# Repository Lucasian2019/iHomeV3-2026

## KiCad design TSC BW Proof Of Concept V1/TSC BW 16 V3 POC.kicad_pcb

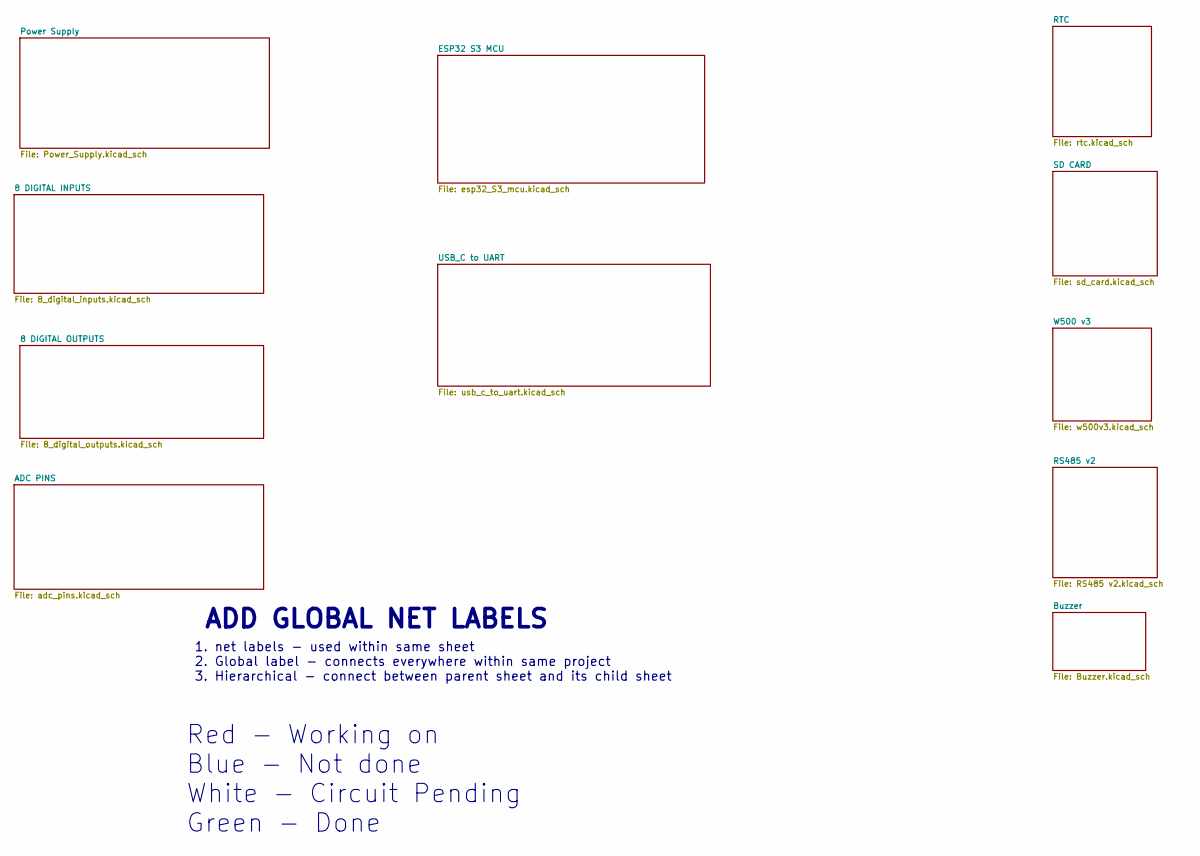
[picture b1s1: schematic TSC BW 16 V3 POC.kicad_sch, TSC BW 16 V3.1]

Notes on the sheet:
ADD GLOBAL NET LABELS
1. net labels - used within same sheet 2. Global label - connects everywhere within same project 3. Hierarchical - connect between parent sheet and its child sheet
Red - Working on Blue - Not done White - Circuit Pending Green - Done

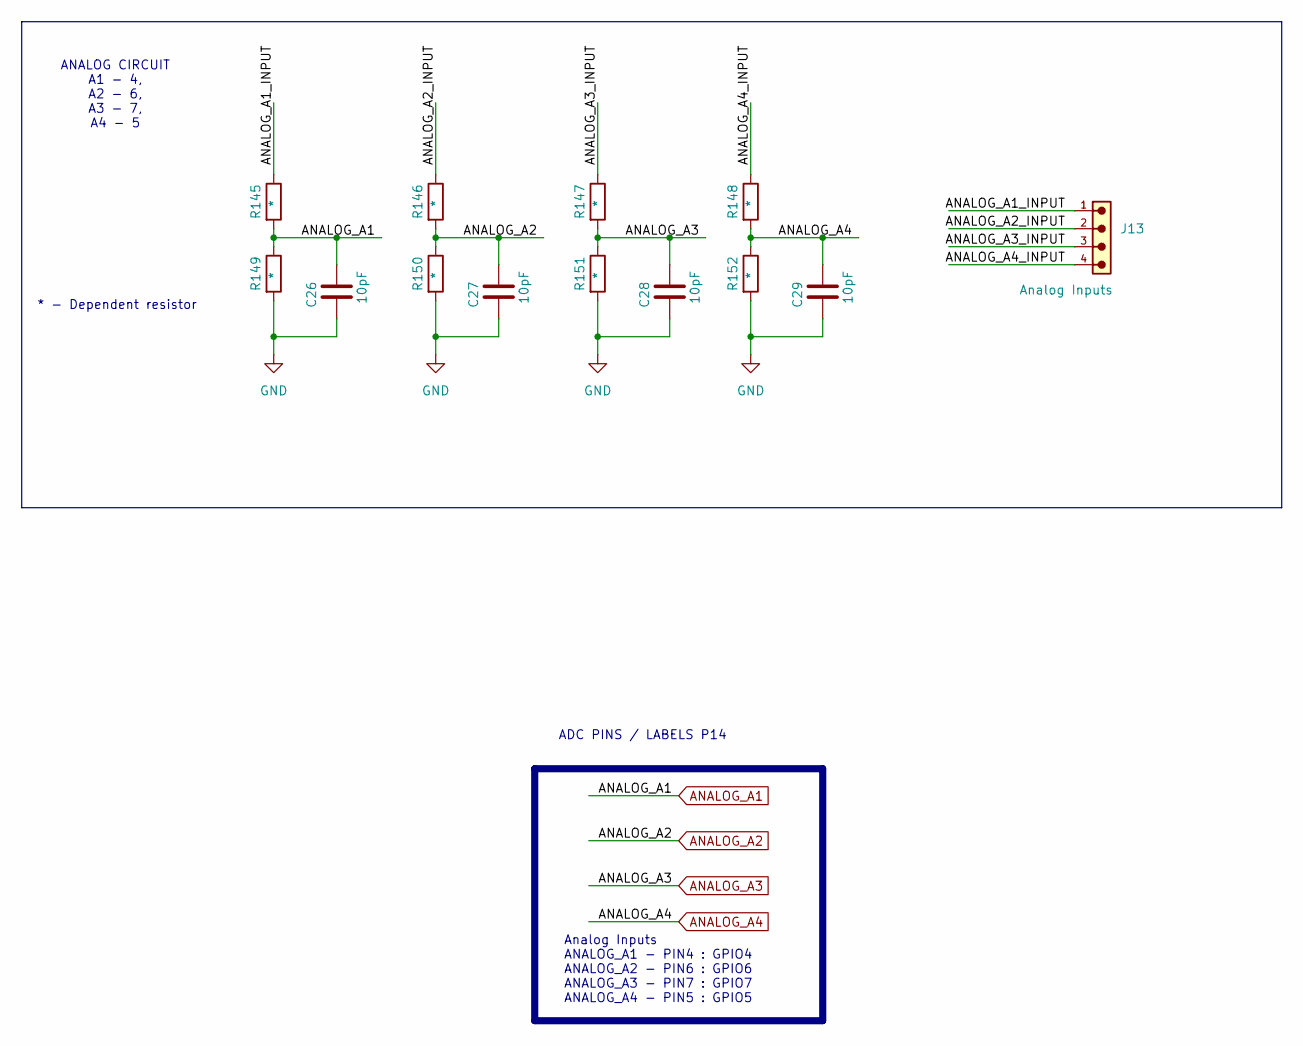
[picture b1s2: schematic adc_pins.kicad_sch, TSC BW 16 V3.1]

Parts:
C26, C27, C28, C29: 10pF; C_1206_3216Metric
J13: Analog Inputs; PhoenixContact_MSTBA_2,5_4-G-5,08_1x04_P5.08mm_Horizontal
R145, R146, R147, R148, R149, R150, R151, R152: *; R_1206_3216Metric_Pad1.30x1.75mm_HandSolder

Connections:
/ADC PINS/ANALOG_A1_INPUT: J13.1, R145.1
/ADC PINS/ANALOG_A2_INPUT: J13.2, R146.1
/ADC PINS/ANALOG_A3_INPUT: J13.3, R147.1
/ADC PINS/ANALOG_A4_INPUT: J13.4, R148.1
ANALOG_A1: C26.2, R145.2, R149.1; also elsewhere on the board
ANALOG_A2: C27.2, R146.2, R150.1; also elsewhere on the board
ANALOG_A3: C28.2, R147.2, R151.1; also elsewhere on the board
ANALOG_A4: C29.2, R148.2, R152.1; also elsewhere on the board
GND: C26.1, C27.1, C28.1, C29.1, R149.2, R150.2, R151.2, R152.2; also elsewhere on the board

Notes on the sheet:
ADC PINS / LABELS P14
Analog Inputs ANALOG_A1 - PIN4 : GPIO4 ANALOG_A2 - PIN6 : GPIO6 ANALOG_A3 - PIN7 : GPIO7 ANALOG_A4 - PIN5 : GPIO5
ANALOG CIRCUIT A1 - 4, A2 - 6, A3 - 7, A4 - 5
* - Dependent resistor

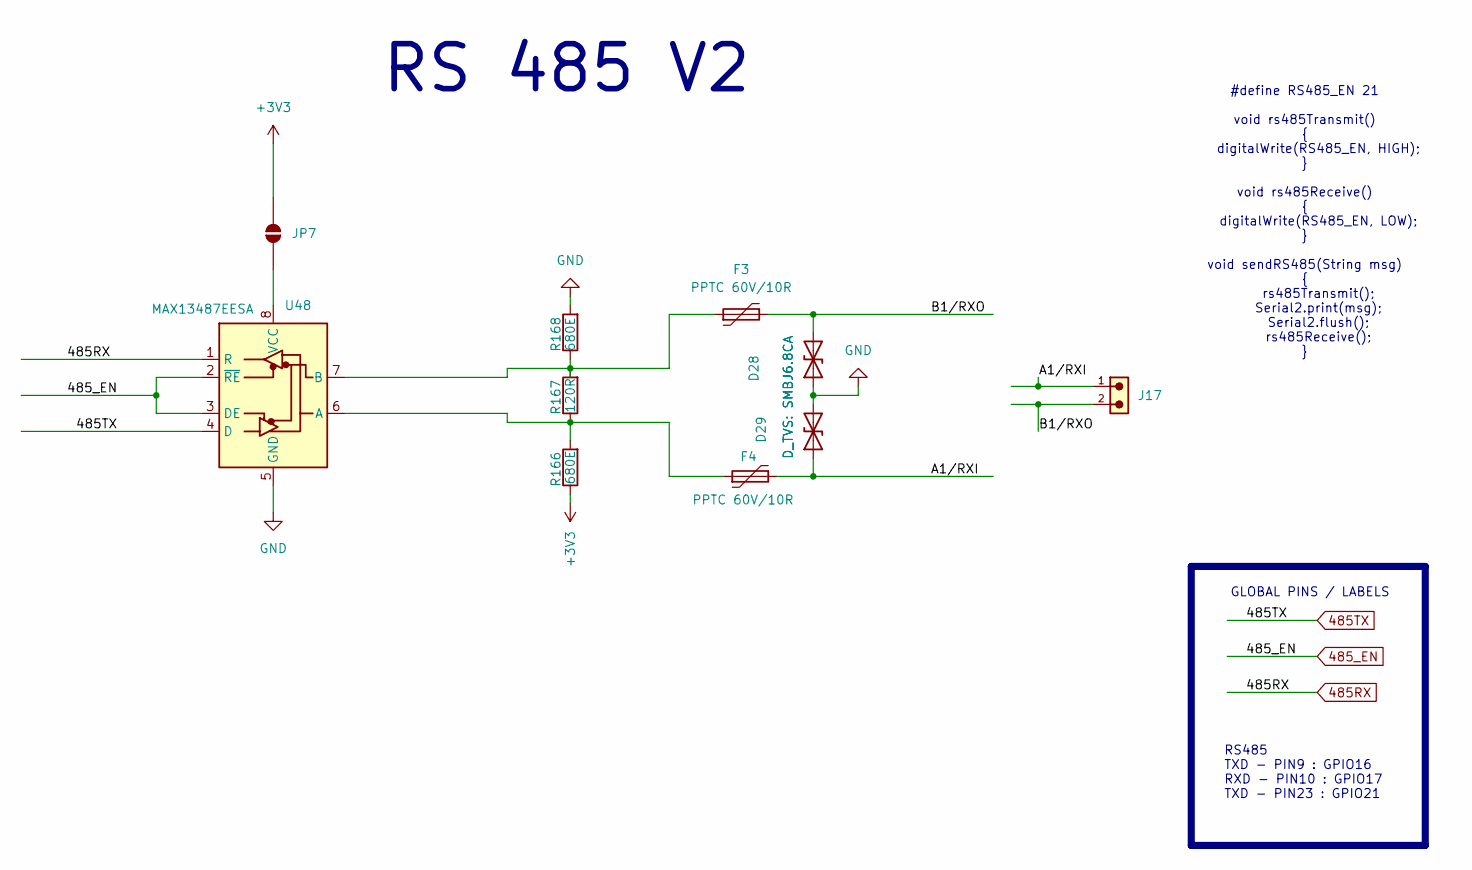
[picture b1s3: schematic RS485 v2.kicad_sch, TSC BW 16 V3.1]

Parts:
D28, D29: D_TVS: SMBJ6.8CA; D_SMB
F3, F4: PPTC 60V/10R; Fuse_1206_3216Metric
J17: 691312510002; PhoenixContact_MSTBA_2,5_2-G-5,08_1x02_P5.08mm_Horizontal
JP7: SolderJumper_2_Open; SolderJumper-2_P1.3mm_Open_RoundedPad1.0x1.5mm
R166, R168: 680E; R_1206_3216Metric_Pad1.30x1.75mm_HandSolder
R167: 120R; R_1206_3216Metric_Pad1.30x1.75mm_HandSolder
U48: MAX13487EESA; SOIC-8_3.9x4.9mm_P1.27mm

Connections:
485RX: U48.1 (R); also elsewhere on the board
485TX: U48.4 (D); also elsewhere on the board
485_EN: U48.2 (~RE), U48.3 (DE); also elsewhere on the board
+3V3: JP7.1 (A), R166.1; also elsewhere on the board
/RS485 v2/A1/RXI: D29.1 (A1), F4.2, J17.1
/RS485 v2/B1/RXO: D28.2 (A2), F3.2, J17.2
GND: D28.1 (A1), D29.2 (A2), R168.2, U48.5 (GND); also elsewhere on the board
unnamed: JP7.2 (B), U48.8 (VCC)
unnamed: F4.1, R166.2, R167.1, U48.6 (A)
unnamed: F3.1, R167.2, R168.1, U48.7 (B)

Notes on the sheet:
RS 485 V2
GLOBAL PINS / LABELS
#define RS485_EN 21 void rs485Transmit() { digitalWrite(RS485_EN, HIGH); } void rs485Receive() { digitalWrite(RS485_EN, LOW); } void sendRS485(String msg) { rs485Transmit(); Serial2.print(msg); Serial2.flush(); rs485Receive(); }
RS485 TXD - PIN9 : GPIO16 RXD - PIN10 : GPIO17 TXD - PIN23 : GPIO21

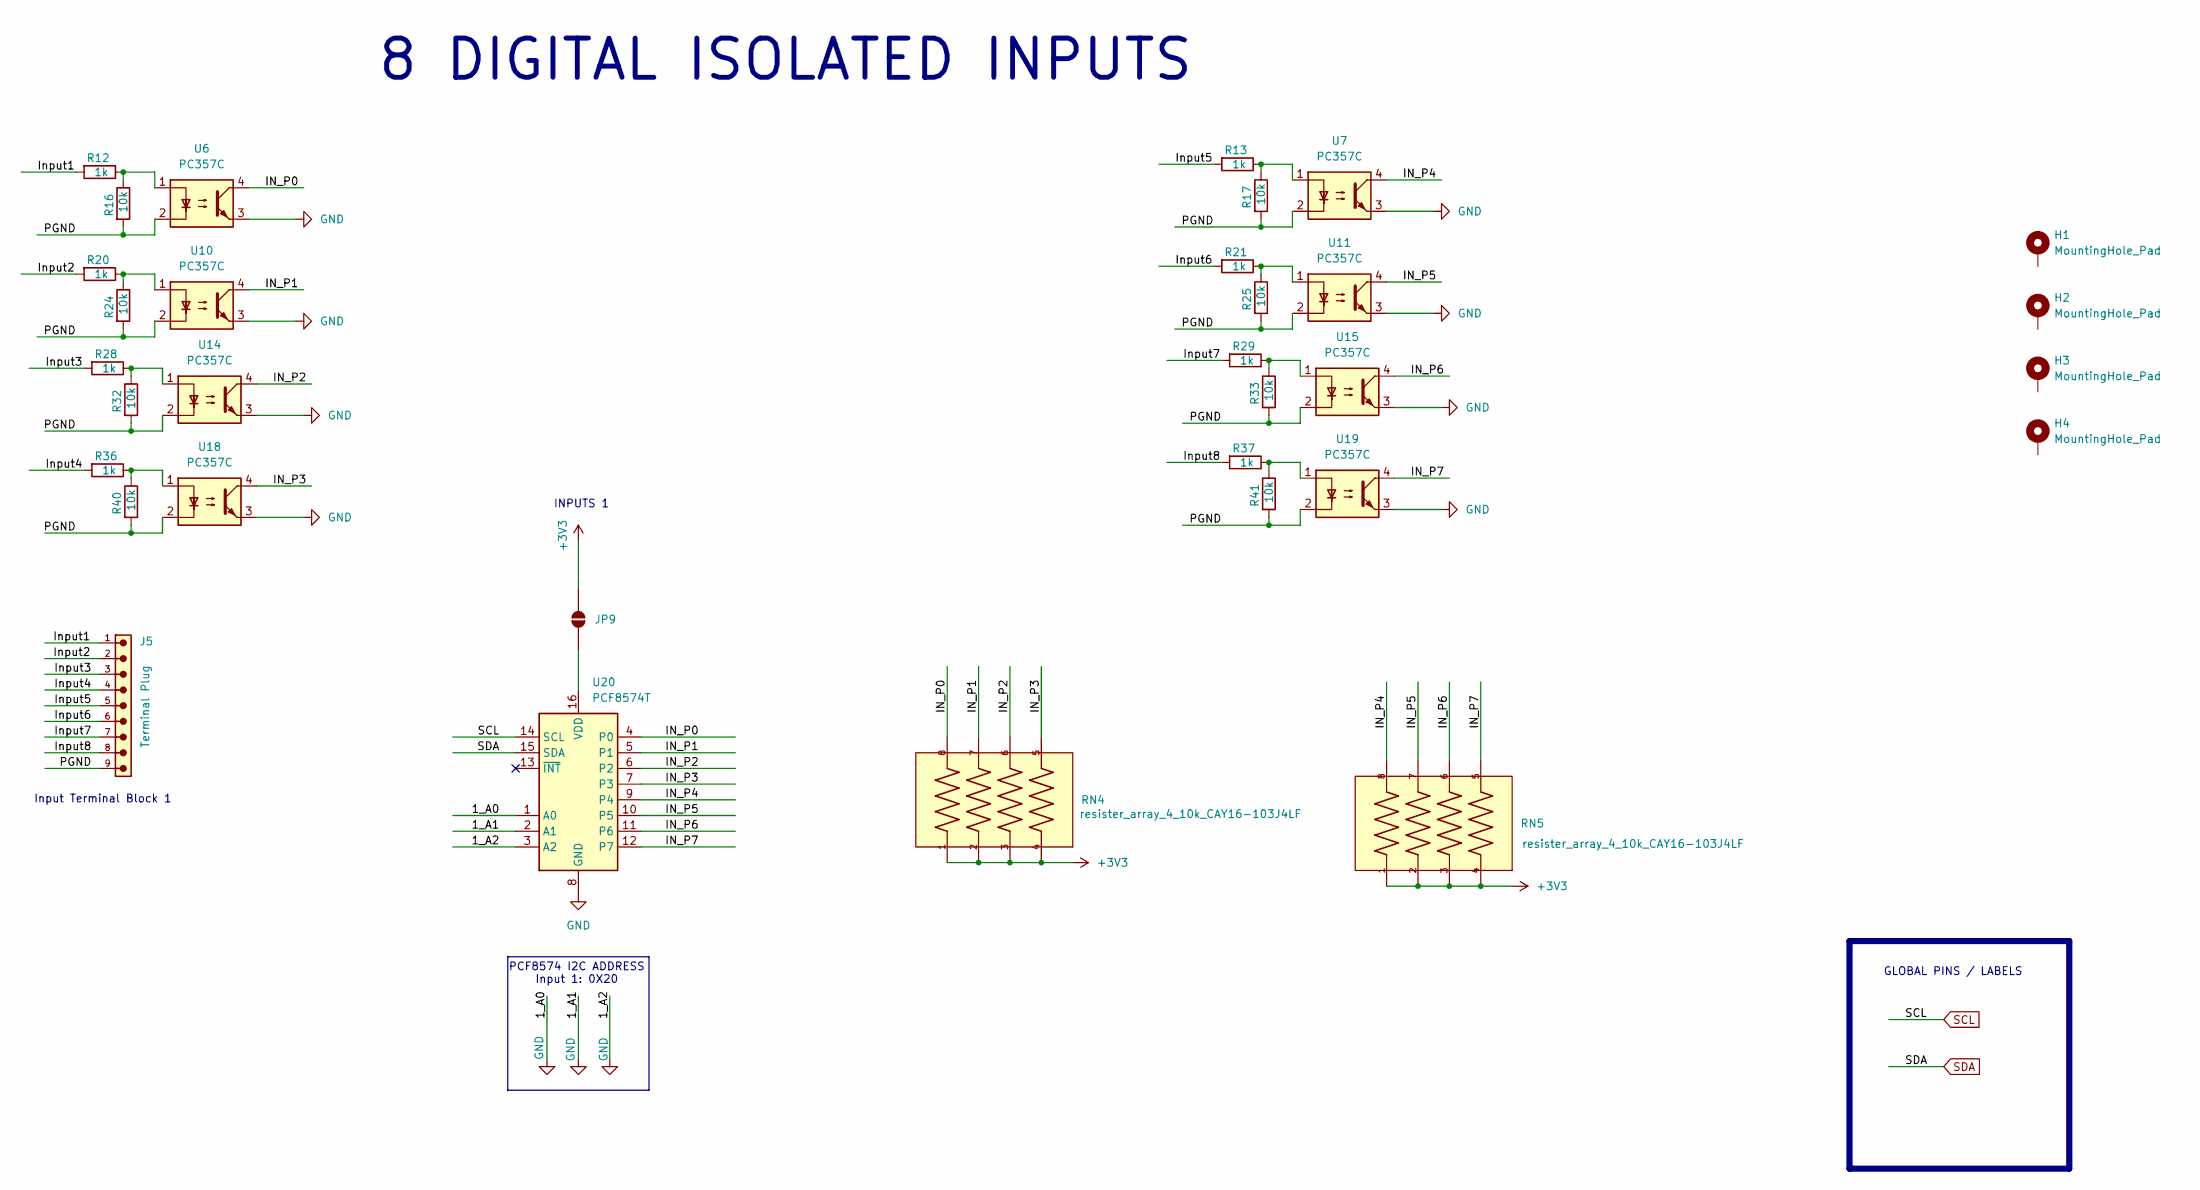
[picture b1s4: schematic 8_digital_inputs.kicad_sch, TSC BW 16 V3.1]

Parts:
H1, H2, H3, H4: MountingHole_Pad; MountingHole_3.2mm_M3_Pad_Via
J5: Terminal Plug; PhoenixContact_MSTBA_2,5_9-G-5,08_1x09_P5.08mm_Horizontal
JP9: SolderJumper_2_Open; SolderJumper-2_P1.3mm_Open_RoundedPad1.0x1.5mm
R12, R13, R20, R21, R28, R29, R36, R37: 1k; R_1206_3216Metric_Pad1.30x1.75mm_HandSolder
R16, R17, R24, R25, R32, R33, R40, R41: 10k; R_1206_3216Metric_Pad1.30x1.75mm_HandSolder
RN4, RN5: resister_array_4_10k_CAY16-103J4LF; R_Array_Convex_4x1206
U6, U7, U10, U11, U14, U15, U18, U19: PC357C; SO-4_4.4x4.3mm_P2.54mm
U20: PCF8574T; SOIC-16W_7.5x10.3mm_P1.27mm

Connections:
+3V3: JP9.1 (A), RN4.1, RN4.2, RN4.3, RN4.4, RN5.1, RN5.2, RN5.3, RN5.4; also elsewhere on the board
/8 DIGITAL INPUTS/IN_P0: RN4.8, U6.4, U20.4 (P0)
/8 DIGITAL INPUTS/IN_P1: RN4.7, U10.4, U20.5 (P1)
/8 DIGITAL INPUTS/IN_P2: RN4.6, U14.4, U20.6 (P2)
/8 DIGITAL INPUTS/IN_P3: RN4.5, U18.4, U20.7 (P3)
/8 DIGITAL INPUTS/IN_P4: RN5.8, U7.4, U20.9 (P4)
/8 DIGITAL INPUTS/IN_P5: RN5.7, U11.4, U20.10 (P5)
/8 DIGITAL INPUTS/IN_P6: RN5.6, U15.4, U20.11 (P6)
/8 DIGITAL INPUTS/IN_P7: RN5.5, U19.4, U20.12 (P7)
/8 DIGITAL INPUTS/Input1: J5.1, R12.2
/8 DIGITAL INPUTS/Input2: J5.2, R20.2
/8 DIGITAL INPUTS/Input3: J5.3, R28.2
/8 DIGITAL INPUTS/Input4: J5.4, R36.2
/8 DIGITAL INPUTS/Input5: J5.5, R13.2
/8 DIGITAL INPUTS/Input6: J5.6, R21.2
/8 DIGITAL INPUTS/Input7: J5.7, R29.2
/8 DIGITAL INPUTS/Input8: J5.8, R37.2
/8 DIGITAL INPUTS/PGND: J5.9, R16.2, R17.2, R24.2, R25.2, R32.2, R33.2, R40.2, R41.2, U6.2, U7.2, U10.2, U11.2, U14.2, U15.2, U18.2, U19.2
GND: U6.3, U7.3, U10.3, U11.3, U14.3, U15.3, U18.3, U19.3, U20.1 (A0), U20.2 (A1), U20.3 (A2), U20.8 (GND); also elsewhere on the board
unnamed: JP9.2 (B), U20.16 (VDD)
unnamed: R12.1, R16.1, U6.1
unnamed: R13.1, R17.1, U7.1
unnamed: R20.1, R24.1, U10.1
unnamed: R21.1, R25.1, U11.1
unnamed: R28.1, R32.1, U14.1
unnamed: R29.1, R33.1, U15.1
unnamed: R36.1, R40.1, U18.1
unnamed: R37.1, R41.1, U19.1
SCL: U20.14 (SCL); also elsewhere on the board
SDA: U20.15 (SDA); also elsewhere on the board

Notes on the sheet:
8 DIGITAL ISOLATED INPUTS
INPUTS 1
Input Terminal Block 1
GLOBAL PINS / LABELS
PCF8574 I2C ADDRESS Input 1: 0X20

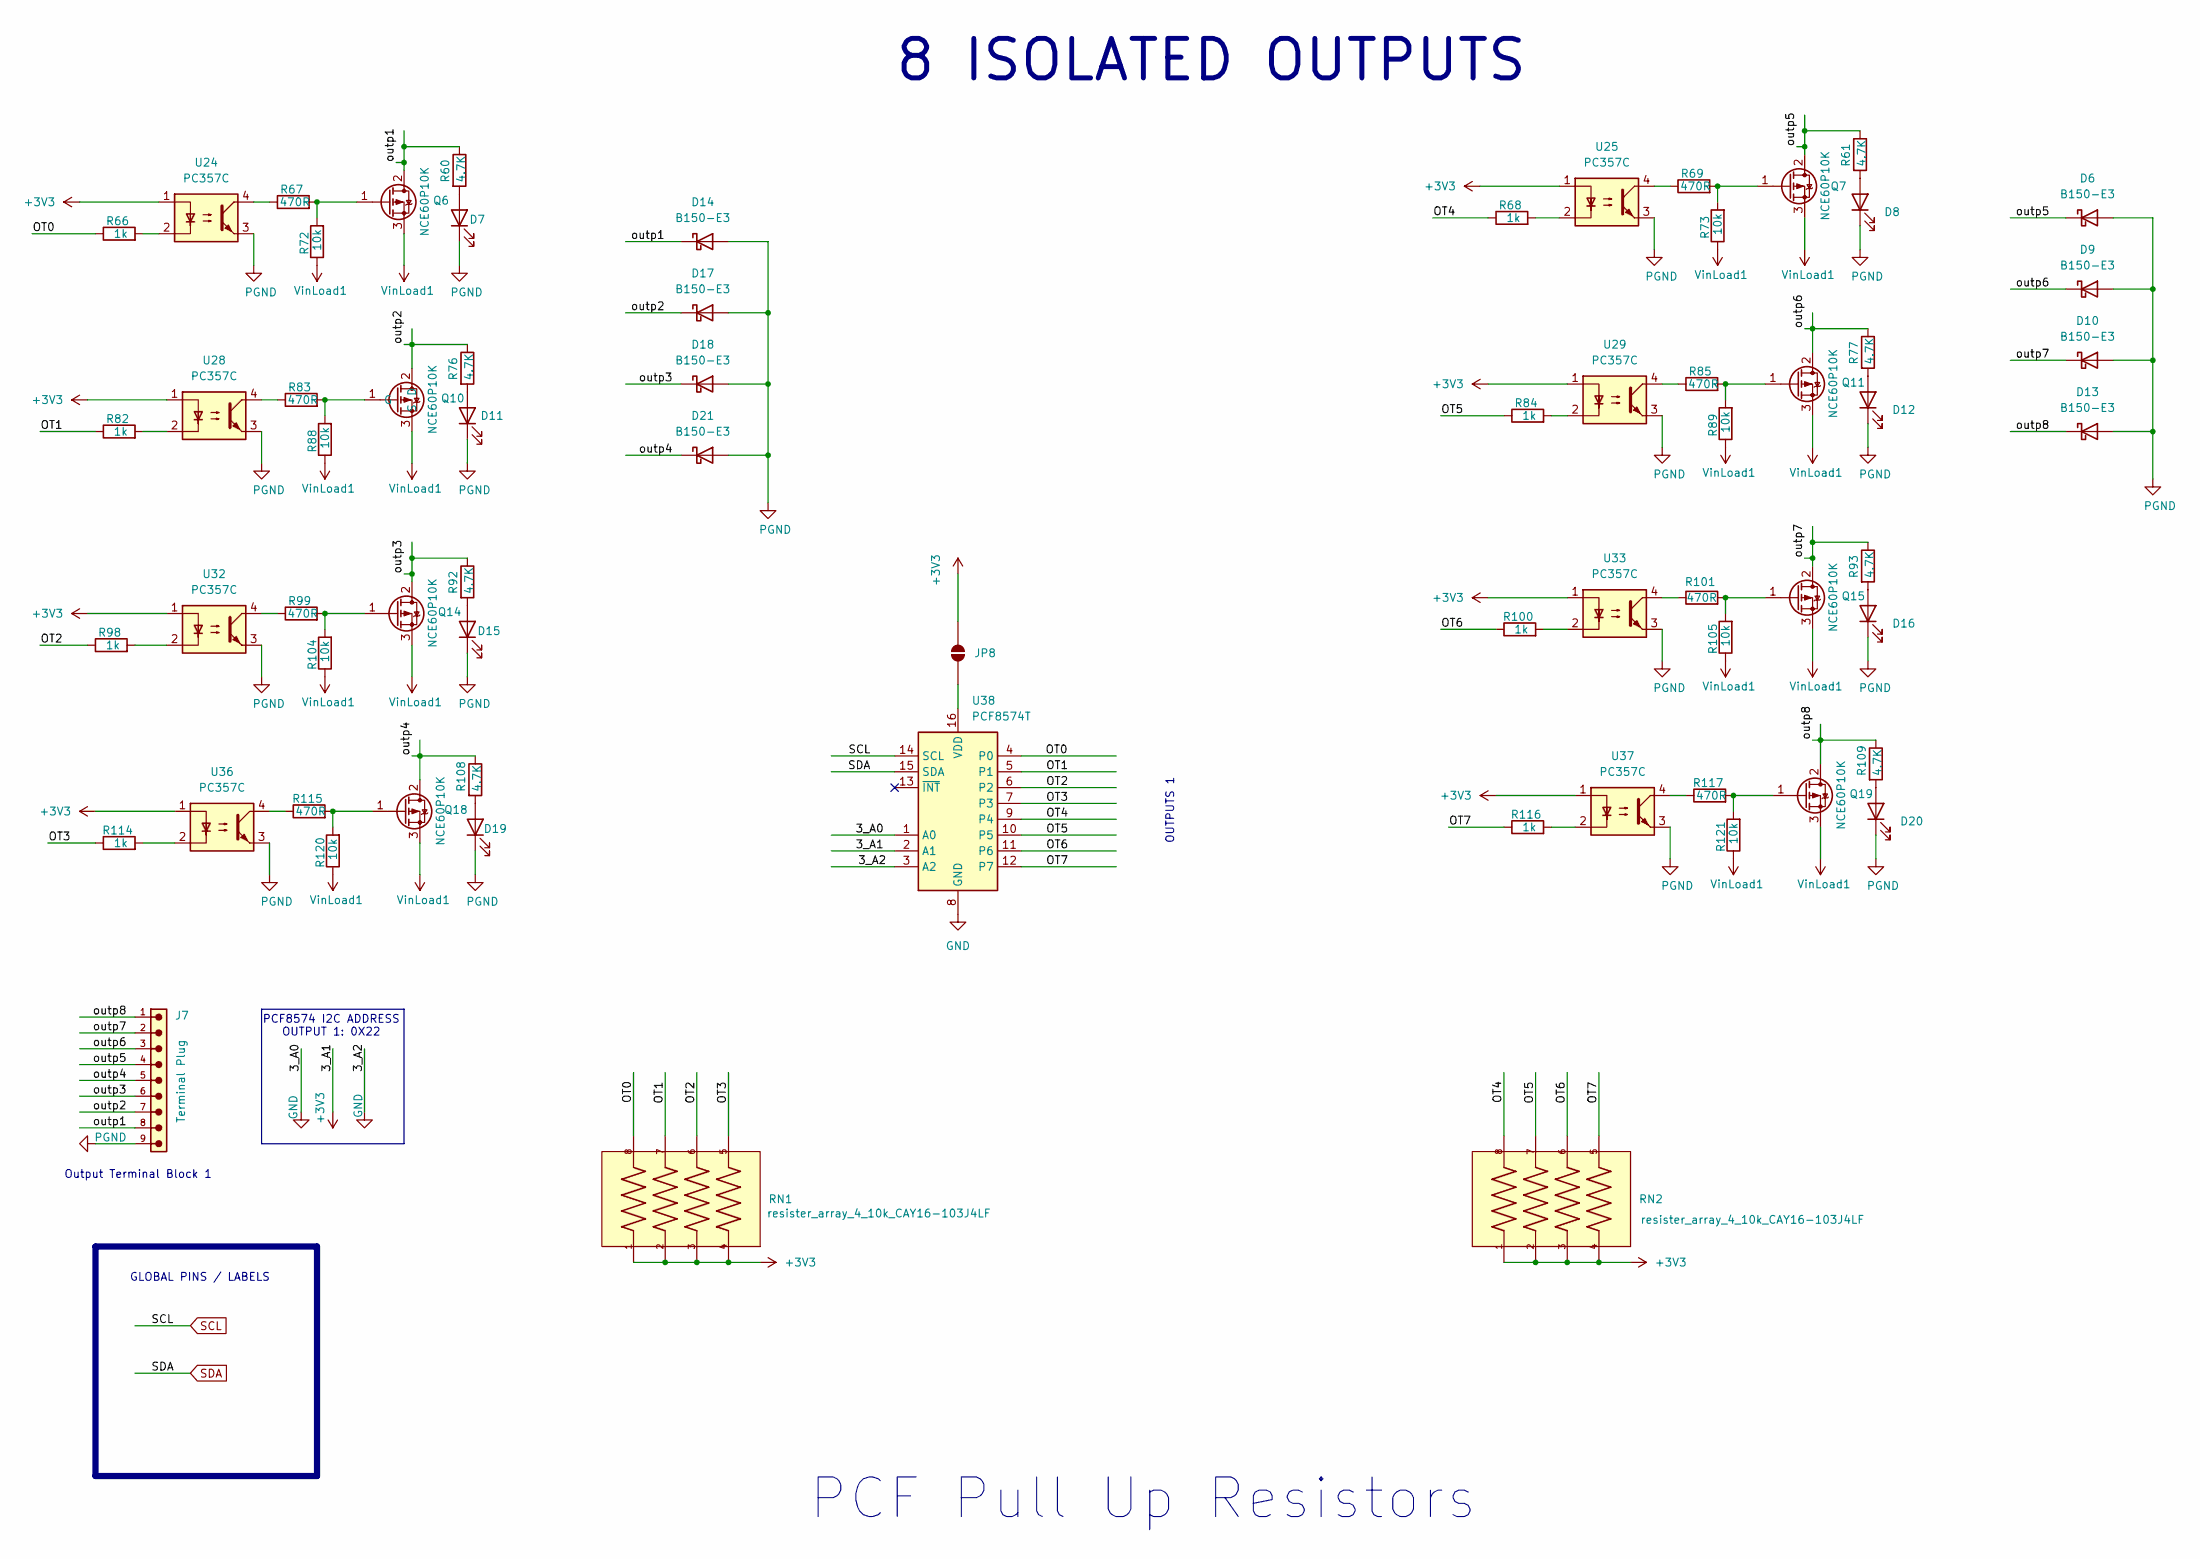
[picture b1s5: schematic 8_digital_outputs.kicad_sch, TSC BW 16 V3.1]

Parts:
D6, D9, D10, D13, D14, D17, D18, D21: B150-E3; D_SMA
D7, D11, D15, D19: IR26-21C_L110_TR8; LED_1206_3216Metric
D8, D12, D16, D20: IR26-21C_L110_TR8; LED_1206_3216Metric_Pad1.42x1.75mm_HandSolder
J7: Terminal Plug; PhoenixContact_MSTBA_2,5_9-G-5,08_1x09_P5.08mm_Horizontal
JP8: SolderJumper_2_Open; SolderJumper-2_P1.3mm_Open_RoundedPad1.0x1.5mm
Q6, Q7, Q10, Q11, Q14, Q15, Q18, Q19: NCE60P10K; TO-252-2
R60, R61, R76, R77, R92, R93, R108, R109: 4.7K; R_1206_3216Metric_Pad1.30x1.75mm_HandSolder
R66, R68, R82, R84, R98, R100, R114, R116: 1k; R_1206_3216Metric_Pad1.30x1.75mm_HandSolder
R67, R69, R83, R85, R99, R101, R115, R117: 470R; R_1206_3216Metric_Pad1.30x1.75mm_HandSolder
R72, R73, R88, R89, R104, R105, R120, R121: 10k; R_1206_3216Metric_Pad1.30x1.75mm_HandSolder
RN1, RN2: resister_array_4_10k_CAY16-103J4LF; R_Array_Convex_4x1206
U24, U25, U28, U29, U32, U33, U36, U37: PC357C; SO-4_4.4x4.3mm_P2.54mm
U38: PCF8574T; SOIC-16W_7.5x10.3mm_P1.27mm

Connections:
+3V3: JP8.2 (B), RN1.1, RN1.2, RN1.3, RN1.4, RN2.1, RN2.2, RN2.3, RN2.4, U24.1, U25.1, U28.1, U29.1, U32.1, U33.1, U36.1, U37.1, U38.2 (A1); also elsewhere on the board
/8 DIGITAL OUTPUTS/OT0: R66.1, RN1.8, U38.4 (P0)
/8 DIGITAL OUTPUTS/OT1: R82.1, RN1.7, U38.5 (P1)
/8 DIGITAL OUTPUTS/OT2: R98.1, RN1.6, U38.6 (P2)
/8 DIGITAL OUTPUTS/OT3: R114.1, RN1.5, U38.7 (P3)
/8 DIGITAL OUTPUTS/OT4: R68.1, RN2.8, U38.9 (P4)
/8 DIGITAL OUTPUTS/OT5: R84.1, RN2.7, U38.10 (P5)
/8 DIGITAL OUTPUTS/OT6: R100.1, RN2.6, U38.11 (P6)
/8 DIGITAL OUTPUTS/OT7: R116.1, RN2.5, U38.12 (P7)
/8 DIGITAL OUTPUTS/outp1: D14.1 (K), J7.8, Q6.2 (D), R60.1
/8 DIGITAL OUTPUTS/outp2: D17.1 (K), J7.7, Q10.2 (D), R76.1
/8 DIGITAL OUTPUTS/outp3: D18.1 (K), J7.6, Q14.2 (D), R92.1
/8 DIGITAL OUTPUTS/outp4: D21.1 (K), J7.5, Q18.2 (D), R108.1
/8 DIGITAL OUTPUTS/outp5: D6.1 (K), J7.4, Q7.2 (D), R61.1
/8 DIGITAL OUTPUTS/outp6: D9.1 (K), J7.3, Q11.2 (D), R77.1
/8 DIGITAL OUTPUTS/outp7: D10.1 (K), J7.2, Q15.2 (D), R93.1
/8 DIGITAL OUTPUTS/outp8: D13.1 (K), J7.1, Q19.2 (D), R109.1
GND: U38.1 (A0), U38.3 (A2), U38.8 (GND); also elsewhere on the board
unnamed: D7.2 (A), R60.2
unnamed: D8.2 (A), R61.2
unnamed: D11.2 (A), R76.2
unnamed: D12.2 (A), R77.2
unnamed: D15.2 (A), R92.2
unnamed: D16.2 (A), R93.2
unnamed: D19.2 (A), R108.2
unnamed: D20.2 (A), R109.2
unnamed: JP8.1 (A), U38.16 (VDD)
unnamed: Q6.1 (G), R67.2, R72.2
unnamed: Q7.1 (G), R69.2, R73.2
unnamed: Q10.1 (G), R83.2, R88.2
unnamed: Q11.1 (G), R85.2, R89.2
unnamed: Q14.1 (G), R99.2, R104.2
unnamed: Q15.1 (G), R101.2, R105.2
unnamed: Q18.1 (G), R115.2, R120.2
unnamed: Q19.1 (G), R117.2, R121.2
unnamed: R66.2, U24.2
unnamed: R67.1, U24.4
unnamed: R68.2, U25.2
unnamed: R69.1, U25.4
unnamed: R82.2, U28.2
unnamed: R83.1, U28.4
unnamed: R84.2, U29.2
unnamed: R85.1, U29.4
unnamed: R98.2, U32.2
unnamed: R99.1, U32.4
unnamed: R100.2, U33.2
unnamed: R101.1, U33.4
unnamed: R114.2, U36.2
unnamed: R115.1, U36.4
unnamed: R116.2, U37.2
unnamed: R117.1, U37.4
PGND: D6.2 (A), D7.1 (K), D8.1 (K), D9.2 (A), D10.2 (A), D11.1 (K), D12.1 (K), D13.2 (A), D14.2 (A), D15.1 (K), D16.1 (K), D17.2 (A), D18.2 (A), D19.1 (K), D20.1 (K), D21.2 (A), J7.9, U24.3, U25.3, U28.3, U29.3, U32.3, U33.3, U36.3, U37.3
SCL: U38.14 (SCL); also elsewhere on the board
SDA: U38.15 (SDA); also elsewhere on the board
VinLoad1: Q6.3 (S), Q7.3 (S), Q10.3 (S), Q11.3 (S), Q14.3 (S), Q15.3 (S), Q18.3 (S), Q19.3 (S), R72.1, R73.1, R88.1, R89.1, R104.1, R105.1, R120.1, R121.1

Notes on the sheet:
GLOBAL PINS / LABELS
PCF8574 I2C ADDRESS OUTPUT 1: 0X22
8 ISOLATED OUTPUTS
OUTPUTS 1
PCF Pull Up Resistors
Output Terminal Block 1

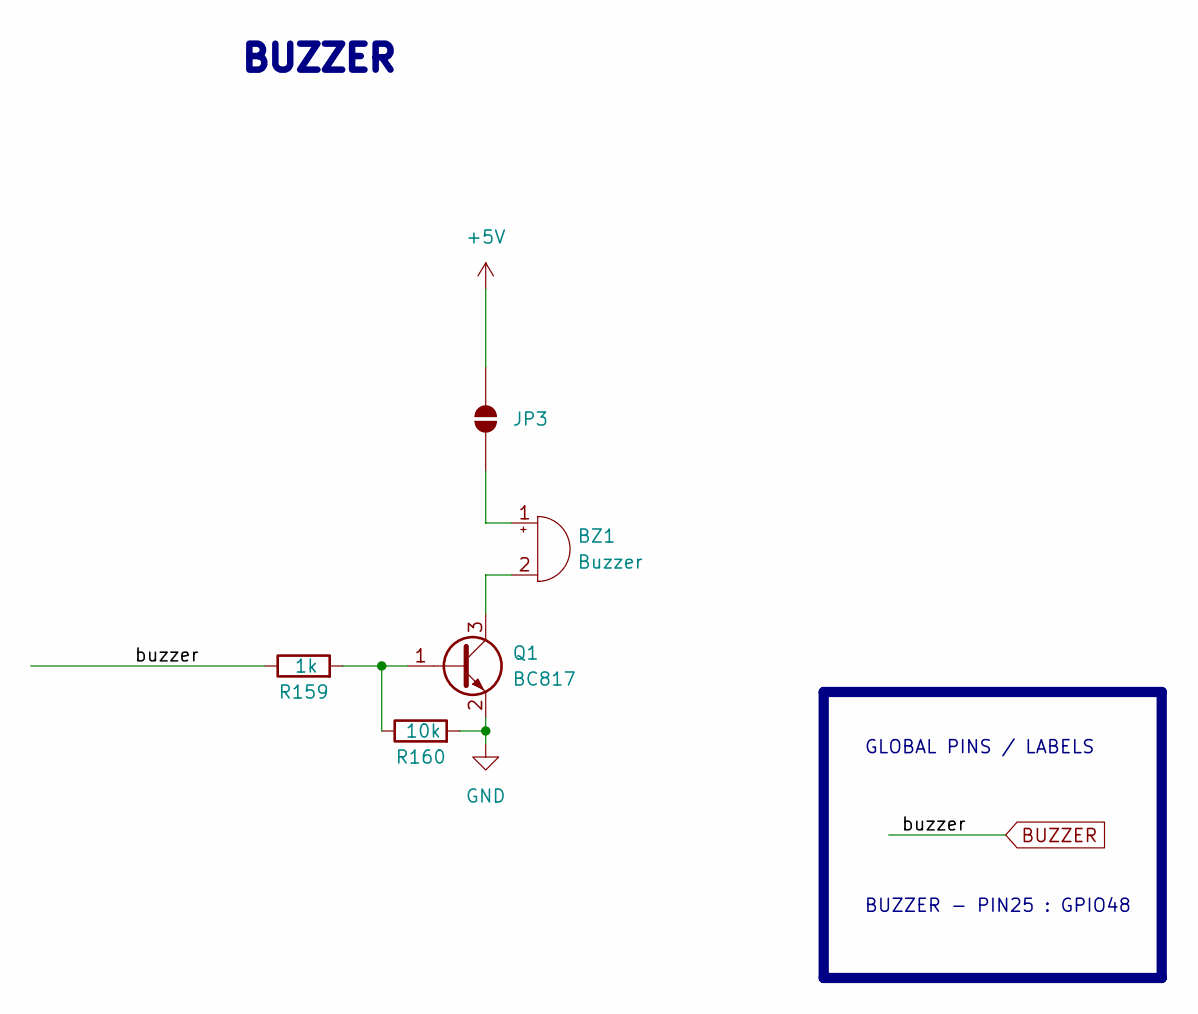
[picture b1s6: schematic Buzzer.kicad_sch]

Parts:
BZ1: Buzzer; Buzzer_15x7.5RM7.6
JP3: SolderJumper_2_Open; SolderJumper-2_P1.3mm_Open_RoundedPad1.0x1.5mm
Q1: BC817; SOT-23
R159: 1k; R_1206_3216Metric_Pad1.30x1.75mm_HandSolder
R160: 10k; R_1206_3216Metric_Pad1.30x1.75mm_HandSolder

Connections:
+5V: JP3.2 (B); also elsewhere on the board
BUZZER: R159.1; also elsewhere on the board
GND: Q1.2 (E), R160.2; also elsewhere on the board
unnamed: BZ1.1 (+), JP3.1 (A)
unnamed: BZ1.2 (-), Q1.3 (C)
unnamed: Q1.1 (B), R159.2, R160.1

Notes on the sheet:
BUZZER
GLOBAL PINS / LABELS
BUZZER - PIN25 : GPIO48

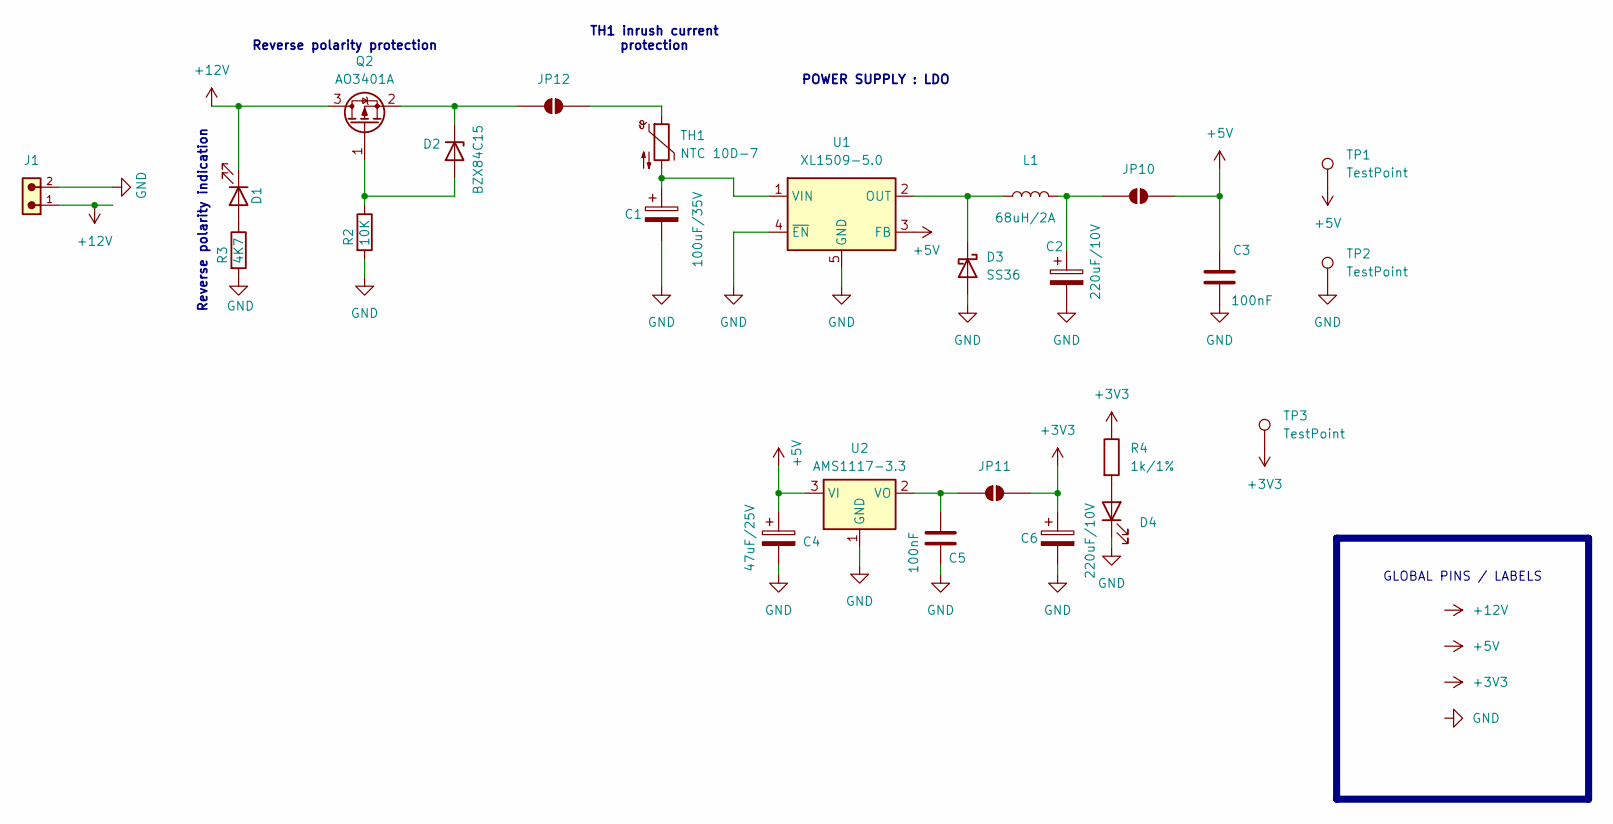
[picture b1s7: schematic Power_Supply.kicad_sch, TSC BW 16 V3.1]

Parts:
C1: 100uF/35V; C_Elec_8x10.2
C2, C6: 220uF/10V; C_Elec_8x10.2
C3, C5: 100nF; C_1206_3216Metric
C4: 47uF/25V; C_Elec_8x10.2
D1, D4: IR26-21C_L110_TR8; LED_1206_3216Metric
D2: BZX84C15; SOT-23
D3: SS36; D_SMA
J1: 691312510002; PhoenixContact_MSTBA_2,5_2-G-5,08_1x02_P5.08mm_Horizontal
JP10, JP11, JP12: SolderJumper_2_Open; SolderJumper-2_P1.3mm_Open_RoundedPad1.0x1.5mm
L1: 68uH/2A; L_Bourns_SRR1260
Q2: AO3401A; SOT-23
R2: 10K; R_1206_3216Metric_Pad1.30x1.75mm_HandSolder
R3: 4K7; R_1206_3216Metric_Pad1.30x1.75mm_HandSolder
R4: 1k/1%; R_1206_3216Metric_Pad1.30x1.75mm_HandSolder
TH1: NTC 10D-7; Fuse_BelFuse_0ZRE0012FF_L8.3mm_W3.8mm
TP1, TP2, TP3: TestPoint; TestPoint_Pad_2.5x2.5mm
U1: XL1509-5.0; SOIC-8_3.9x4.9mm_P1.27mm
U2: AMS1117-3.3; SOT-223-3_TabPin2

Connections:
+3V3: C6.1, JP11.2 (B), R4.1, TP3.1 (1_1); also elsewhere on the board
+5V: C3.1, C4.1, JP10.2 (B), TP1.1 (1_1), U1.3 (FB), U2.3 (VI); also elsewhere on the board
+12V: D1.1 (K), J1.1, Q2.3 (D)
GND: C1.2, C2.2, C3.2, C4.2, C5.2, C6.2, D3.2 (A), D4.1 (K), J1.2, R2.2, R3.2, TP2.1 (1_1), U1.4 (~EN), U1.5 (GND), U1.6 (GND), U1.7 (GND), U1.8 (GND), U2.1 (GND); also elsewhere on the board
unnamed: D1.2 (A), R3.1
unnamed: D2.1 (A), Q2.1 (G), R2.1
unnamed: D2.3 (K), JP12.1 (A), Q2.2 (S)
unnamed: D3.1 (K), L1.1, U1.2 (OUT)
unnamed: D4.2 (A), R4.2
unnamed: C2.1, JP10.1 (A), L1.2
unnamed: C5.1, JP11.1 (A), U2.2 (VO)
unnamed: JP12.2 (B), TH1.1
unnamed: C1.1, TH1.2, U1.1 (VIN)

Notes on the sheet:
POWER SUPPLY : LDO
Reverse polarity protection
Reverse polarity indication
TH1 inrush current protection
GLOBAL PINS / LABELS

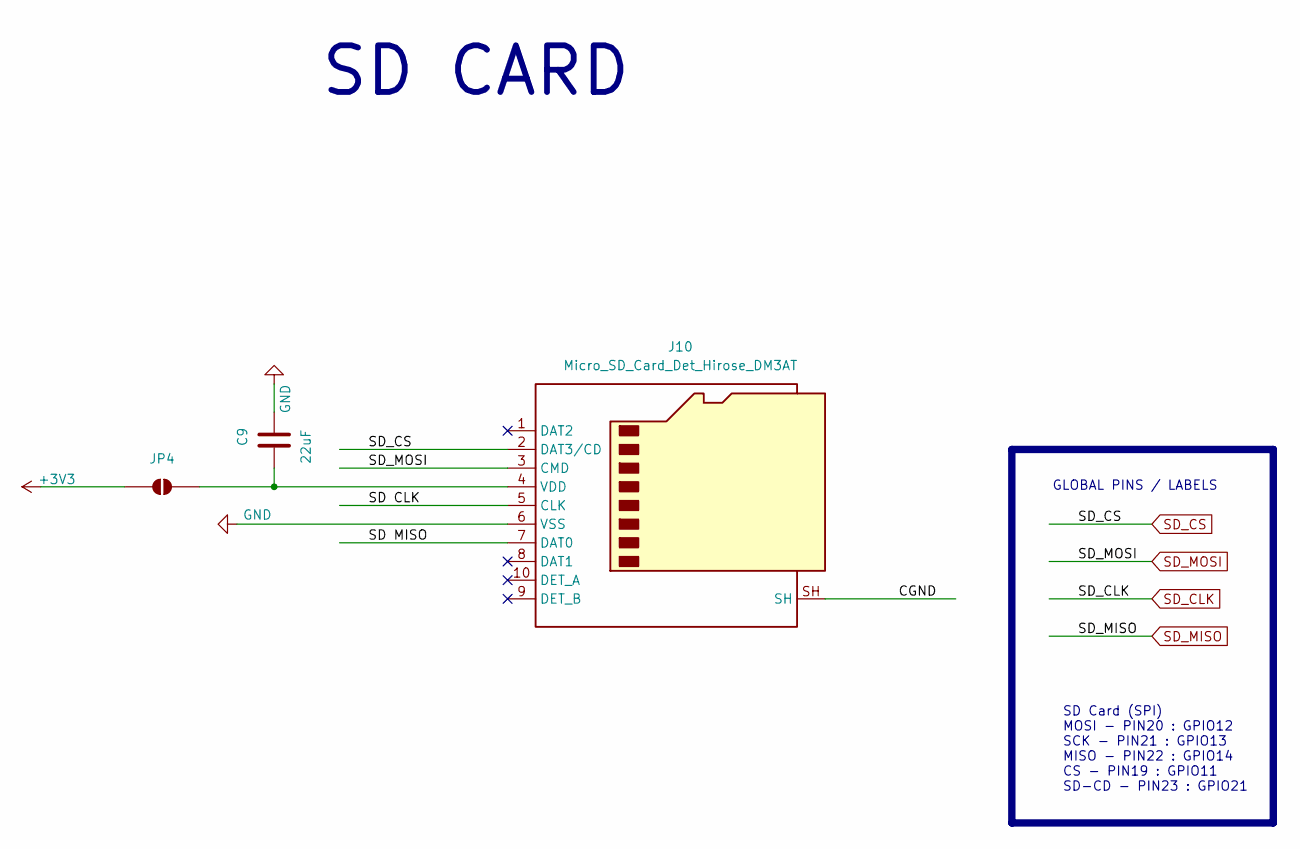
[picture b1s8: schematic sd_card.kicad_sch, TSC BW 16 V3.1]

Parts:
C9: 22uF; C_1206_3216Metric
J10: Micro_SD_Card_Det_Hirose_DM3AT; microSD_HC_Hirose_DM3AT-SF-PEJM5
JP4: SolderJumper_2_Open; SolderJumper-2_P1.3mm_Open_RoundedPad1.0x1.5mm

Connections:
+3V3: JP4.1 (A); also elsewhere on the board
/SD CARD/CGND: J10.SH
/SD CARD/SD CLK: J10.5 (CLK)
/SD CARD/SD MISO: J10.7 (DAT0)
GND: C9.2, J10.6 (VSS); also elsewhere on the board
unnamed: C9.1, J10.4 (VDD), JP4.2 (B)
SD_CS: J10.2 (DAT3/CD); also elsewhere on the board
SD_MOSI: J10.3 (CMD); also elsewhere on the board

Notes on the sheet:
SD CARD
GLOBAL PINS / LABELS
SD Card (SPI) MOSI - PIN20 : GPIO12 SCK - PIN21 : GPIO13 MISO - PIN22 : GPIO14 CS - PIN19 : GPIO11 SD-CD - PIN23 : GPIO21

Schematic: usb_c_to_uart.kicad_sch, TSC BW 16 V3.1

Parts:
C22: 10nF; C_1206_3216Metric
C23, C24, C25: 100nF; C_1206_3216Metric
D22: SS36; D_SMA
D23, D24, D25: LESD5D5.0CT1G; D_SOD-523; PARTREV O
J14: USB_C_Receptacle_USB2.0_16P; USB_C_Receptacle_GCT_USB4105-xx-A_16P_TopMnt_Horizontal
JP6: SolderJumper_2_Open; SolderJumper-2_P1.3mm_Open_RoundedPad1.0x1.5mm
Q20, Q21: SS8050; SOT-23
R153, R155: 5.1k; R_1206_3216Metric_Pad1.30x1.75mm_HandSolder
R154, R156, R157, R158: 10k; R_1206_3216Metric_Pad1.30x1.75mm_HandSolder
SW1, SW2: SW_Push; SW_SPST_PTS647_Sx38
U44: CH340C; SOIC-16_3.9x9.9mm_P1.27mm

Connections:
+3V3: R157.1, R158.1; also elsewhere on the board
+5V: JP6.1 (A); also elsewhere on the board
/USB_C to UART/D+: D24.1, J14.A6 (D+), J14.B6 (D+), U44.5 (UD+)
/USB_C to UART/D-: D25.1, J14.A7 (D-), J14.B7 (D-), U44.6 (UD-)
/USB_C to UART/DTR: Q21.2 (E), R154.1, U44.13 (~DTR)
/USB_C to UART/RST: Q20.2 (E), R156.1, U44.14 (~RTS)
/USB_C to UART/TVS: D22.2 (A), D23.1, J14.A4 (VBUS), J14.A9 (VBUS), J14.B4 (VBUS), J14.B9 (VBUS), U44.16 (VCC)
EN: C24.1, Q20.3 (C), R157.2, SW1.1; also elsewhere on the board
GND: C22.1, C23.2, C24.2, C25.2, D23.2, D24.2, D25.2, J14.A1 (GND), J14.A12 (GND), J14.B1 (GND), J14.B12 (GND), J14.SH (SHIELD), R153.2, R155.2, SW1.2, SW2.2, U44.1 (GND); also elsewhere on the board
IO0: C25.1, Q21.3 (C), R158.2, SW2.1; also elsewhere on the board
unnamed: C23.1, D22.1 (K), JP6.2 (B)
unnamed: J14.A5 (CC1), R153.1
unnamed: J14.B5 (CC2), R155.1
unnamed: Q20.1 (B), R154.2
unnamed: Q21.1 (B), R156.2
unnamed: C22.2, U44.4 (V3)
RXD: U44.2 (TXD); also elsewhere on the board
TXD: U44.3 (RXD); also elsewhere on the board

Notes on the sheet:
USB - TO - UART
USB C - UART EN- PIN3 : NO GPIO IO0 - PIN27 : GPIO0 RXD - PIN36/RXD0 : GPIO44,U0RXD TXD - PIN37/ TXD0 : GPIO43,U0TXD
AUTO PROGRAM
GLOBAL PINS / LABELS

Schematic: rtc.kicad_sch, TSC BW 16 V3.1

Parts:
C43, C44: 0.1uF; C_1206_3216Metric
J2: CR1220_S8411_45R; BatteryHolder_Keystone_500; PARTREV 4
JP2: SolderJumper_2_Open; SolderJumper-2_P1.3mm_Open_RoundedPad1.0x1.5mm
U40: AT24CS04-SSHM; SOIC-8_3.9x4.9mm_P1.27mm
U41: DS3231MZ; SOIC-8_3.9x4.9mm_P1.27mm

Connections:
+3V3: JP2.2 (B); also elsewhere on the board
GND: C43.2, C44.2, J2.2, U40.2 (A1), U40.3 (A2), U40.4 (GND), U40.7 (WP), U41.5 (GND); also elsewhere on the board
unnamed: C43.1, C44.1, JP2.1 (A), U40.8 (VCC), U41.2 (VCC)
unnamed: J2.1, U41.6 (VBAT)
SCL: U40.6 (SCL), U41.8 (SCL); also elsewhere on the board
SDA: U40.5 (SDA), U41.7 (SDA); also elsewhere on the board

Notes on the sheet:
DS3231 I2C ADDRESS 0x68 Fixed
GLOBAL PINS / LABELS
RTC DS3231 & 24C04 EEPROM
24C04 I2C ADDRESS 0x50 (A1 & A2 -> GND)
